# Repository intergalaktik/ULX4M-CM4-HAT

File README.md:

# ULX4M-CM4-HAT

###

On V1 we have FTDI to FPGA working and we can upload bitstream to FPGA, serial passtrue is also working.
For some reason it was hard to put ESP32 into bootloader mode, and I was not able to load micropython while shiled was connected to FPGA.
After doing that directly (bricking pins on shield FTDI TX > ESP32 RX, ESP32 TX > FTDI RX, GPIO0 > GND) I have succesfully loaded micropython on ESP32.
WROOM is still not perfect fit as it has low memory.
WROWER can access shared SD card, and flash FPGA over WIFI.

### Current pinout

cm4_gpio|wifi_gpio|HAT function|FPGA|FPGA
--- | --- | --- | --- | --
0 | 21 | SDA0 | P17 |
1 | 22 | SCL0 | P16 |
2 | 12 | SD_D2 | K1 | K5
3 | 4 | SD_D1 | H1 | J5
4 | 2 | SD_D0 | J3 | K4
5 | 33 | | H16 |
6 |  | BTN1 | R1 |
7 |  | BTN2 | P3 |
8 | 19 | | P4 |
9 | 27 | | G16 |
10 | 26 | | N17 |
11 | 25 | | L16 |
12 | 23 | TDI | R5 |
13 |  | FTDI_TXDEN | T1 |
14 | 13 | SD_D3 | K2 | L4
15 | 14 | SD_CLK | H2 | L5
16 | 34 | TDO | V4 | 
17 | 35 | | N17 |
18 | | LED1 | N5 |
19 | 0 | BOOT_PULL_UP | U1
20 | 18 | TCK | T5 |
21 | 5 | TMS | U5 |
22 | EN | WIFI_EN | U18
23 |  | FTDI_TXD | N4 |
24 |  | FTDI_RX | N3 |
25 | RXD0 | WIFI_RDX | P5 |
26 | TXD0 | WIFI_TXD | V1 |
27 | 15 | SD_CMD | J1 | N16

### ToDo

- [x] FTDI chip
- [x] USB
- [x] FTDI JTAG connected to FPGA
- [x] FTDI UART connected to FPGA
- [x] ESP32 UART connected to FPGA
- [x] ESP32 connected to SD card that is connected to FPGA ( SD card sharing )
- [x] LEDS
- [x] BTNS
- [ ] USBC
- [ ] 8 LEDs
- [ ] 8 BTNs
- [ ] ESP32 WROM
- [ ] ESP32 WROVER
- [ ] ESP32 S2 
- [ ] ESP32 S3
- [ ] FT4232
- [ ] USB A host connector connected directly to FPGA
- [ ] I2S Audio
- [ ] Audio amplifier
- [ ] PMOD connector/connectors

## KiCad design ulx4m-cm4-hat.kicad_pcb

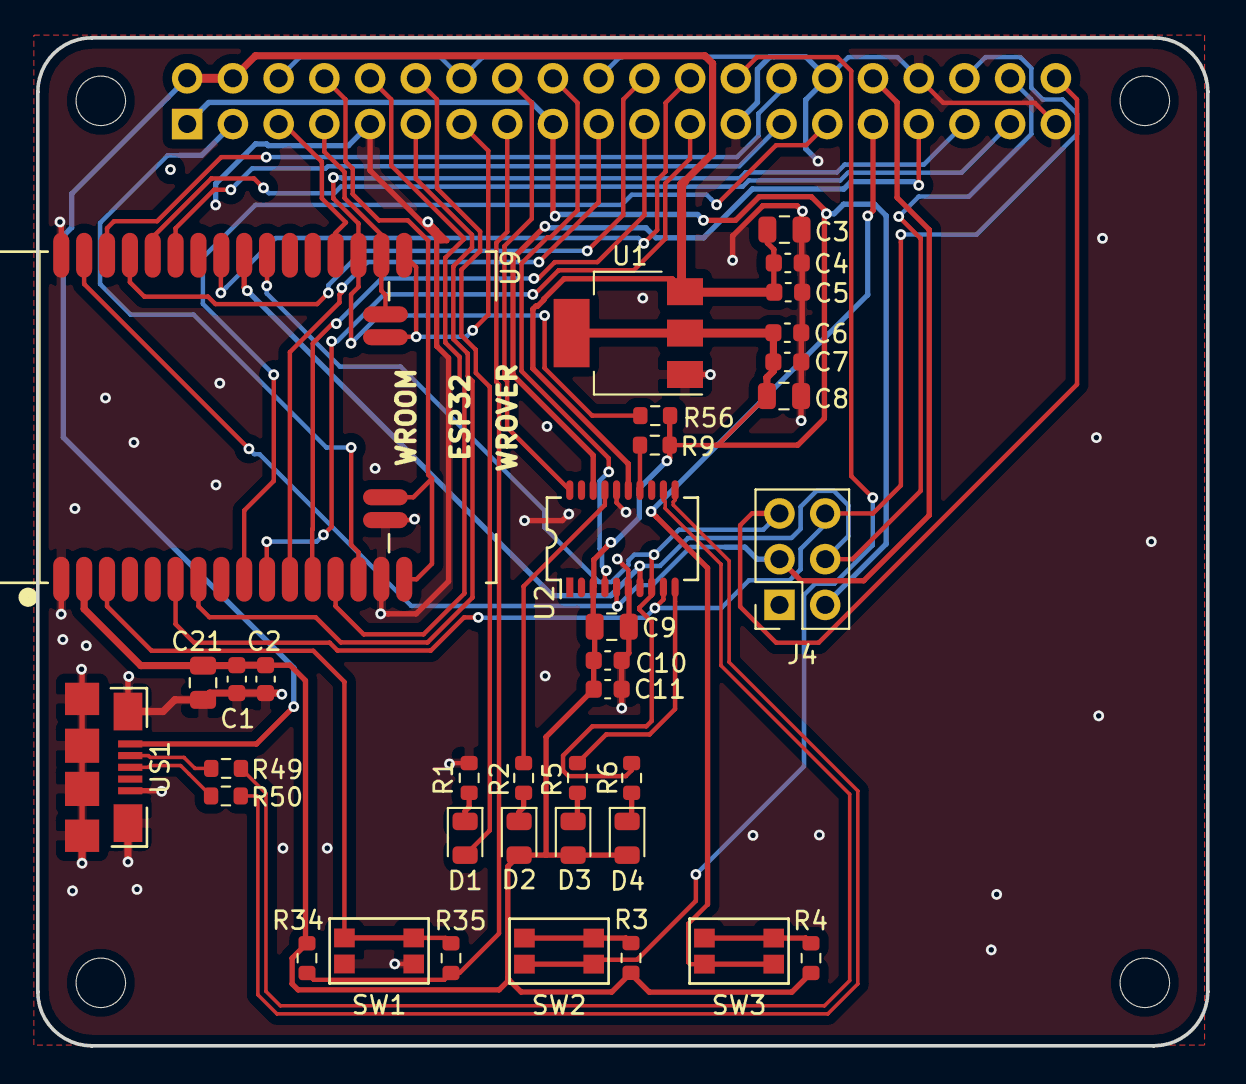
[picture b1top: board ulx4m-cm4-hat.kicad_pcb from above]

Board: 4 copper layers, 65.0 x 56.0 mm, 41 parts (1 on the bottom side), 45 nets.

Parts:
C1, C4, C6, C10: 100n; C_0603_1608Metric
C2, C5, C7, C11: 10n; C_0603_1608Metric
C3, C8, C9, C21: 22uF; C_0805_2012Metric
D1, D4: R; LED_0805_2012Metric
D2: B; LED_0805_2012Metric
D3: G; LED_0805_2012Metric
H1, H2, H5, H6: MountingHole; MountingHole_2.75mm_NoPad
J1: Raspberry_Pi_2_3; PinSocket_2x20_P2.54mm_Vertical
J4: CONN_02X03; PinSocket_2x03_P2.54mm_Vertical
R1, R2, R5, R6, R35: 549; R_0603_1608Metric
R3, R4: 1K; R_0603_1608Metric
R9, R34, R56: 15k; R_0603_1608Metric
R49, R50: 27; R_0603_1608Metric
SW1: WIFI ENABLE; Switch_EVPAA
SW2: BTN2; Switch_EVPAA
SW3: BTN1; Switch_EVPAA
U1: LM1117-3.3; SOT-223-3_TabPin2
U2: FT231XS; FT231X-SSOP-20_4.4x6.5mm_Pitch0.65mm
U9: ESP32
US1: MICRO_USB; USB-MICRO-B-FCI-10118192-0001LF

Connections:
+3V3: C1.1, C2.1, C6.1, C7.1, C8.1, C9.1, C10.1, C11.1, C21.1, D2.2, D3.2, D4.2, J1.1, J1.17, J4.2, R3.1, R4.1, R9.2, R34.1, R56.1, U1.2, U2.3, U9.2
+5V: C3.1, C4.1, C5.1, J1.2, J1.4, U1.3, U2.15, US1.1
/FTD+: R50.2, US1.3
/FTD-: R49.2, US1.2
/WIFIEN: R35.2, SW1.1, U9.3
FTDI_RXD: J1.18, U2.4
FTDI_TXD: J1.16, U2.20
FTDI_TXDEN: J1.33, U2.18
FTDI_nRXLED: R2.1, U2.17
FTDI_nTXLED: R5.1, U2.10
GND: C1.2, C2.2, C3.2, C4.2, C5.2, C6.2, C7.2, C8.2, C9.2, C10.2, C11.2, C21.2, J1.6, J1.9, J1.14, J1.20, J1.25, J1.30, J1.34, J1.39, J4.1, R1.2, SW1.2, U1.1, U2.6, U2.16, U9.1, U9.15, U9.38, US1.5, US1.6
JTAG_TCK: J1.38, J4.4, U2.7, U9.30
JTAG_TDI: J1.32, J4.3, U2.5, U9.37
JTAG_TDO: J1.36, J4.6, U2.9, U9.6
JTAG_TMS: J1.40, J4.5, R6.1, U2.8, U9.29
unnamed: D1.1, R1.1
unnamed: D2.1, R2.2
unnamed: D3.1, R5.2
unnamed: D4.1, R6.2
unnamed: R3.2, SW2.1
unnamed: R4.2, SW3.1
RP_GPIO06: J1.31, SW3.2
RP_GPIO07: J1.26, SW2.2
RP_GPIO18: D1.2, J1.12
SD_CLK: J1.10, U9.13
SD_CMD: J1.13, U9.23
SD_D0: J1.7, U9.24
SD_D1: J1.5, U9.26
SD_D2: J1.3, U9.14
SD_D3: J1.8, U9.16
USB_FTDI_D+: R50.1, U2.11
USB_FTDI_D-: R49.1, U2.12
WIFI_EN: J1.15, R34.2, R35.1
WIFI_GPIO0: J1.35, R56.2, U9.25
WIFI_GPIO19: J1.24, U9.31
WIFI_GPIO21: J1.27, U9.33
WIFI_GPIO22: J1.28, U9.36
WIFI_GPIO25: J1.23, U9.10
WIFI_GPIO26: J1.19, U9.11
WIFI_GPIO27: J1.21, U9.12
WIFI_GPIO33: J1.29, U9.9
WIFI_GPIO35: J1.11, U9.7
WIFI_RXD: J1.37, U9.34
WIFI_TXD: J1.22, U9.35
nRESET: R9.1, U2.14

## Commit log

2021-11-08 Adding initial files
2021-11-10 Version v1.0
2021-12-04 Adding pic folder
2021-12-09 Adding schematics
